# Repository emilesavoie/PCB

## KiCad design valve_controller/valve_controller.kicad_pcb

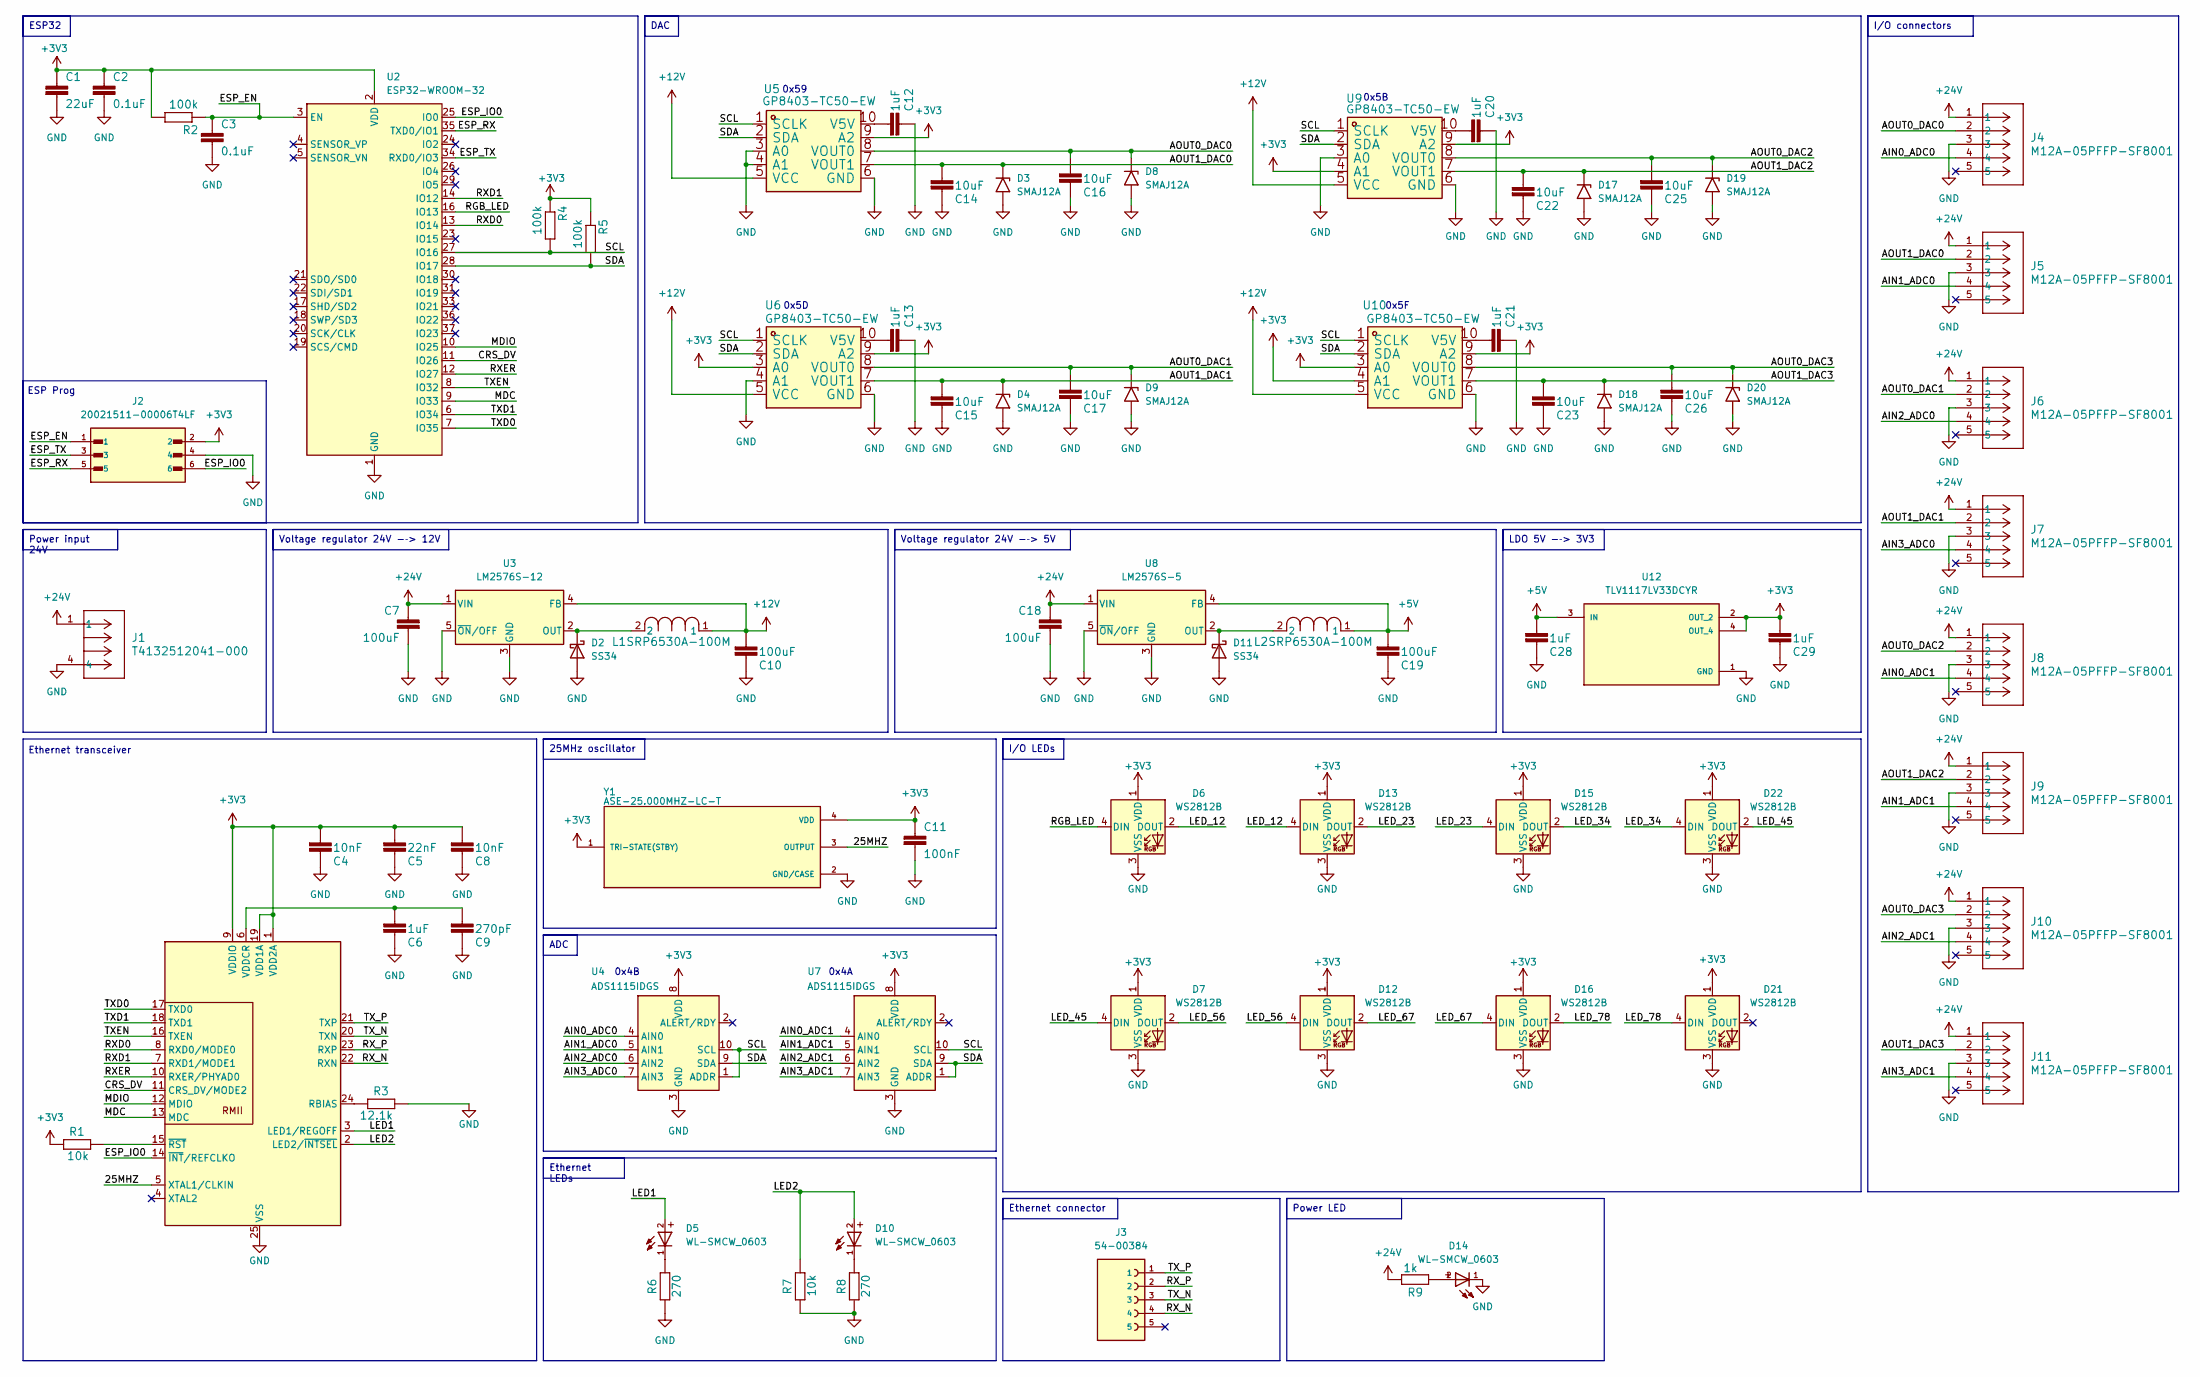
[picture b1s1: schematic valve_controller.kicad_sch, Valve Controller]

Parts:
C1: 22uF; C_0603_1608Metric
C2, C3: 0.1uF; C_0603_1608Metric
C4, C8: 10nF; C_0603_1608Metric
C5: 22nF; C_0603_1608Metric
C6, C12, C13, C20, C21, C28, C29: 1uF; C_0603_1608Metric
C7, C10, C18, C19: 100uF; C_0603_1608Metric
C9: 270pF; C_0603_1608Metric
C11: 100nF; C_0603_1608Metric
C14, C15, C16, C17, C22, C23, C25, C26: 10uF; C_0603_1608Metric
D2, D11: SS34; D_SMA
D3, D4, D8, D9, D17, D18, D19, D20: SMAJ12A; D_SMA
D5, D10, D14: WL-SMCW_0603
D6, D7, D12, D13, D15, D16, D21, D22: WS2812B; LED_WS2812B_PLCC4_5.0x5.0mm_P3.2mm
J1: T4132512041-000; CONN4_T4132512041
J2: 20021511-00006T4LF; AMPHENOL_20021511-00006T4LF; PARTREV C3
J3: 54-00384; 54; PARTREV A
J4, J5, J6, J7, J8, J9, J10, J11: M12A-05PFFP-SF8001; CONN_SF8001_AMP
L1, L2: SRP6530A-100M; IND_SRP6530A_BRN
R1, R7: 10k; R_0603_1608Metric
R2, R4, R5: 100k; R_0603_1608Metric
R3: 12.1k; R_0603_1608Metric
R6, R8: 270; R_0603_1608Metric
R9: 1k; R_0603_1608Metric
U1: LAN8720A; VQFN-24-1EP_4x4mm_P0.5mm_EP2.5x2.5mm_ThermalVias
U2: ESP32-WROOM-32
U3: LM2576S-12; TO-263-5_TabPin3
U4, U7: ADS1115IDGS; TSSOP-10_3x3mm_P0.5mm
U5, U6, U9, U10: GP8403-TC50-EW; ESSOP-10_L4.9-W3.9-P1.00-LS6.0-BL-EP
U8: LM2576S-5; TO-263-5_TabPin3
U12: TLV1117LV33DCYR; VREG_TLV1117LV33DCYR; PARTREV B
Y1: ASE-25.000MHZ-LC-T; XTAL_ASE-25.000MHZ-LC-T; PARTREV 02-18-22

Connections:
+3V3: C1.1, C2.1, C4.2, C5.2, C8.2, C11.1, C29.2, D6.1 (VDD), D7.1 (VDD), D12.1 (VDD), D13.1 (VDD), D15.1 (VDD), D16.1 (VDD), D21.1 (VDD), D22.1 (VDD), J2.2, R1.2, R2.2, R4.1, R5.1, U1.1 (VDD2A), U1.9 (VDDIO), U1.19 (VDD1A), U2.2 (VDD), U4.8 (VDD), U5.9 (A2), U6.3 (A0), U6.9 (A2), U7.8 (VDD), U9.4 (A1), U9.9 (A2), U10.3 (A0), U10.4 (A1), U10.9 (A2), U12.2 (OUT_2), U12.4 (OUT_4), Y1.1 (TRI-STATE(STBY)), Y1.4 (VDD)
+5V: C19.2, C28.2, L2.1, U8.4 (FB), U12.3 (IN)
+12V: C10.2, L1.1, U3.4 (FB), U5.5 (VCC), U6.5 (VCC), U9.5 (VCC), U10.5 (VCC)
+24V: C7.1, C18.1, J1.1, J4.1, J5.1, J6.1, J7.1, J8.1, J9.1, J10.1, J11.1, R9.1, U3.1 (VIN), U8.1 (VIN)
/25MHZ: U1.5 (XTAL1/CLKIN), Y1.3 (OUTPUT)
/AIN0_ADC0: J4.4, U4.4 (AIN0)
/AIN0_ADC1: J8.4, U7.4 (AIN0)
/AIN1_ADC0: J5.4, U4.5 (AIN1)
/AIN1_ADC1: J9.4, U7.5 (AIN1)
/AIN2_ADC0: J6.4, U4.6 (AIN2)
/AIN2_ADC1: J10.4, U7.6 (AIN2)
/AIN3_ADC0: J7.4, U4.7 (AIN3)
/AIN3_ADC1: J11.4, U7.7 (AIN3)
/AOUT0_DAC0: C16.2, D8.1 (A1), J4.2, U5.8 (VOUT0)
/AOUT0_DAC1: C17.2, D9.1 (A1), J6.2, U6.8 (VOUT0)
/AOUT0_DAC2: C25.2, D19.1 (A1), J8.2, U9.8 (VOUT0)
/AOUT0_DAC3: C26.2, D20.1 (A1), J10.2, U10.8 (VOUT0)
/AOUT1_DAC0: C14.2, D3.1 (A1), J5.2, U5.7 (VOUT1)
/AOUT1_DAC1: C15.2, D4.1 (A1), J7.2, U6.7 (VOUT1)
/AOUT1_DAC2: C22.2, D17.1 (A1), J9.2, U9.7 (VOUT1)
/AOUT1_DAC3: C23.2, D18.1 (A1), J11.2, U10.7 (VOUT1)
/CRS_DV: U1.11 (CRS_DV/MODE2), U2.11 (IO26)
/ESP_EN: C3.1, J2.1, R2.1, U2.3 (EN)
/ESP_IO0: J2.6, U1.14 (~INT/REFCLKO), U2.25 (IO0)
/ESP_RX: J2.5, U2.35 (TXD0/IO1)
/ESP_TX: J2.3, U2.34 (RXD0/IO3)
/LED1: D5.2, U1.3 (LED1/REGOFF)
/LED2: D10.2, R7.1, U1.2 (LED2/~INTSEL)
/LED_12: D6.2 (DOUT), D13.4 (DIN)
/LED_23: D13.2 (DOUT), D15.4 (DIN)
/LED_34: D15.2 (DOUT), D22.4 (DIN)
/LED_45: D7.4 (DIN), D22.2 (DOUT)
/LED_56: D7.2 (DOUT), D12.4 (DIN)
/LED_67: D12.2 (DOUT), D16.4 (DIN)
/LED_78: D16.2 (DOUT), D21.4 (DIN)
/MDC: U1.13 (MDC), U2.9 (IO33)
/MDIO: U1.12 (MDIO), U2.10 (IO25)
/RGB_LED: D6.4 (DIN), U2.16 (IO13)
/RXD0: U1.8 (RXD0/MODE0), U2.13 (IO14)
/RXD1: U1.7 (RXD1/MODE1), U2.14 (IO12)
/RXER: U1.10 (RXER/PHYAD0), U2.12 (IO27)
/RX_N: J3.4, U1.22 (RXN)
/RX_P: J3.2, U1.23 (RXP)
/SCL: R4.2, U2.27 (IO16), U4.1 (ADDR), U4.10 (SCL), U5.1 (SCLK), U6.1 (SCLK), U7.10 (SCL), U9.1 (SCLK), U10.1 (SCLK)
/SDA: R5.2, U2.28 (IO17), U4.9 (SDA), U5.2 (SDA), U6.2 (SDA), U7.1 (ADDR), U7.9 (SDA), U9.2 (SDA), U10.2 (SDA)
/TXD0: U1.17 (TXD0), U2.7 (IO35)
/TXD1: U1.18 (TXD1), U2.6 (IO34)
/TXEN: U1.16 (TXEN), U2.8 (IO32)
/TX_N: J3.3, U1.20 (TXN)
/TX_P: J3.1, U1.21 (TXP)
GND: C1.2, C2.2, C3.2, C4.1, C5.1, C6.1, C7.2, C8.1, C9.1, C10.1, C11.2, C12.1, C13.1, C14.1, C15.1, C16.1, C17.1, C18.2, C19.1, C20.1, C21.1, C22.1, C23.1, C25.1, C26.1, C28.1, C29.1, D2.2 (A), D3.2 (A2), D4.2 (A2), D6.3 (VSS), D7.3 (VSS), D8.2 (A2), D9.2 (A2), D11.2 (A), D12.3 (VSS), D13.3 (VSS), D14.1, D15.3 (VSS), D16.3 (VSS), D17.2 (A2), D18.2 (A2), D19.2 (A2), D20.2 (A2), D21.3 (VSS), D22.3 (VSS), J1.4, J2.4, J4.3, J5.3, J6.3, J7.3, J8.3, J9.3, J10.3, J11.3, R3.1, R6.2, R7.2, R8.2, U1.25 (VSS), U2.1 (GND), U2.15 (GND), U2.38 (GND), U2.39 (GND), U3.3 (GND), U3.5 (~ON/OFF), U4.3 (GND), U5.3 (A0), U5.4 (A1), U5.6 (GND), U6.4 (A1), U6.6 (GND), U7.3 (GND), U8.3 (GND), U8.5 (~ON/OFF), U9.3 (A0), U9.6 (GND), U10.6 (GND), U12.1 (GND), Y1.2 (GND/CASE)
unnamed: D2.1 (K), L1.2, U3.2 (OUT)
unnamed: D5.1, R6.1
unnamed: D10.1, R8.1
unnamed: D11.1 (K), L2.2, U8.2 (OUT)
unnamed: D14.2, R9.2
unnamed: R3.2, U1.24 (RBIAS)
unnamed: C6.2, C9.2, U1.6 (VDDCR)
unnamed: R1.1, U1.15 (~RST)
unnamed: C12.2, U5.10 (V5V)
unnamed: C13.2, U6.10 (V5V)
unnamed: C20.2, U9.10 (V5V)
unnamed: C21.2, U10.10 (V5V)

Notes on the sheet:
Voltage regulator 24V -­> 5V
I/O connectors
I/O LEDs
DAC
Power LED
Voltage regulator 24V -­> 12V
ADC
25MHz oscillator
Power input 24V
Ethernet LEDs
LDO 5V -­> 3V3
ESP32
Ethernet connector
0x4B
0x4A
0x5F
0x59
0x5B
Ethernet transceiver
ESP Prog
0x5D

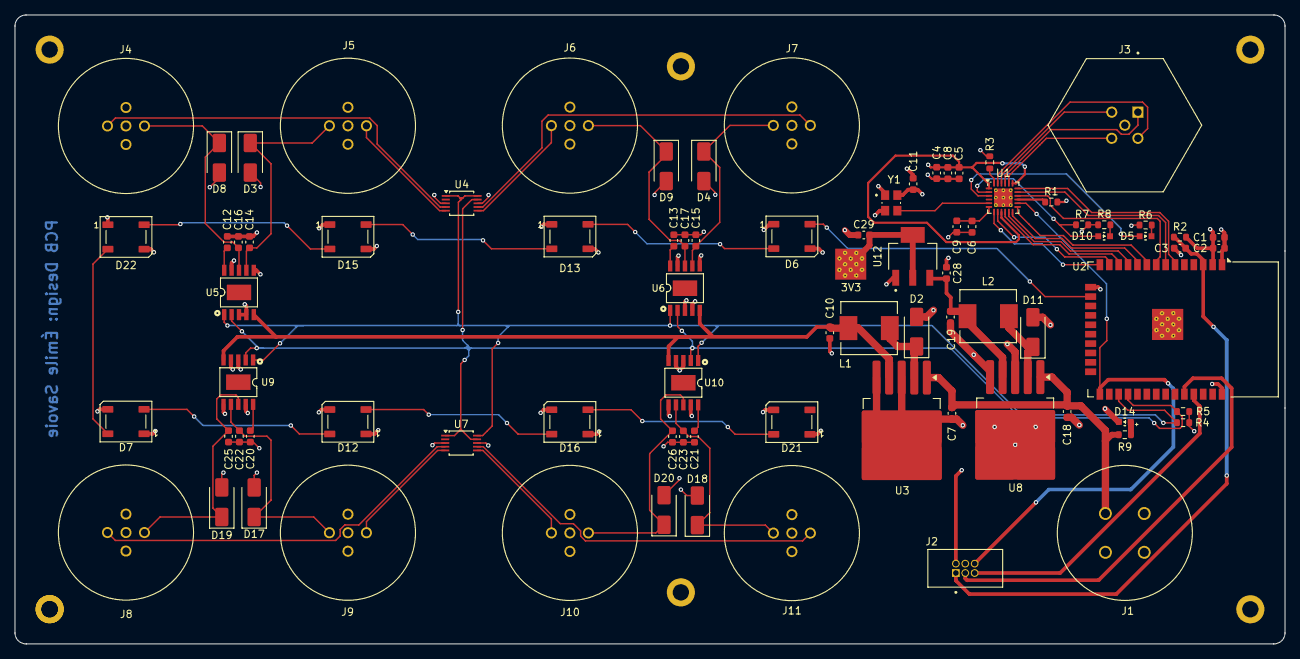
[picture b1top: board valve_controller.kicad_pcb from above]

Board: 4 copper layers, 171.6 x 85.0 mm, 82 parts (0 on the bottom side), 63 nets.

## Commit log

2025-06-16 init
2025-06-16 First base for DAC, ADC and connector
2025-06-17 First base
2025-06-17 modif esp chip and power setup
2025-06-18 Full ethernet interface
2025-06-18 First layout of pcb
    Ready for review
2025-06-20 Updated + ports
2025-06-21 Started pcb layout
2025-06-23 Review 06/23
2025-06-23 new regulator
2025-06-24 Added 12v power bus
2025-06-25 Fully updated DAC and regulators
2025-06-27 Layout V2
2025-06-27 Routing V1
2025-07-01 LED + routing V2
2025-07-02 tweaks for case
2025-07-03 First DRC run
2025-07-04 New ethernet and power routing
2025-07-04 Changes after review
2025-07-07 Updated changes for review
